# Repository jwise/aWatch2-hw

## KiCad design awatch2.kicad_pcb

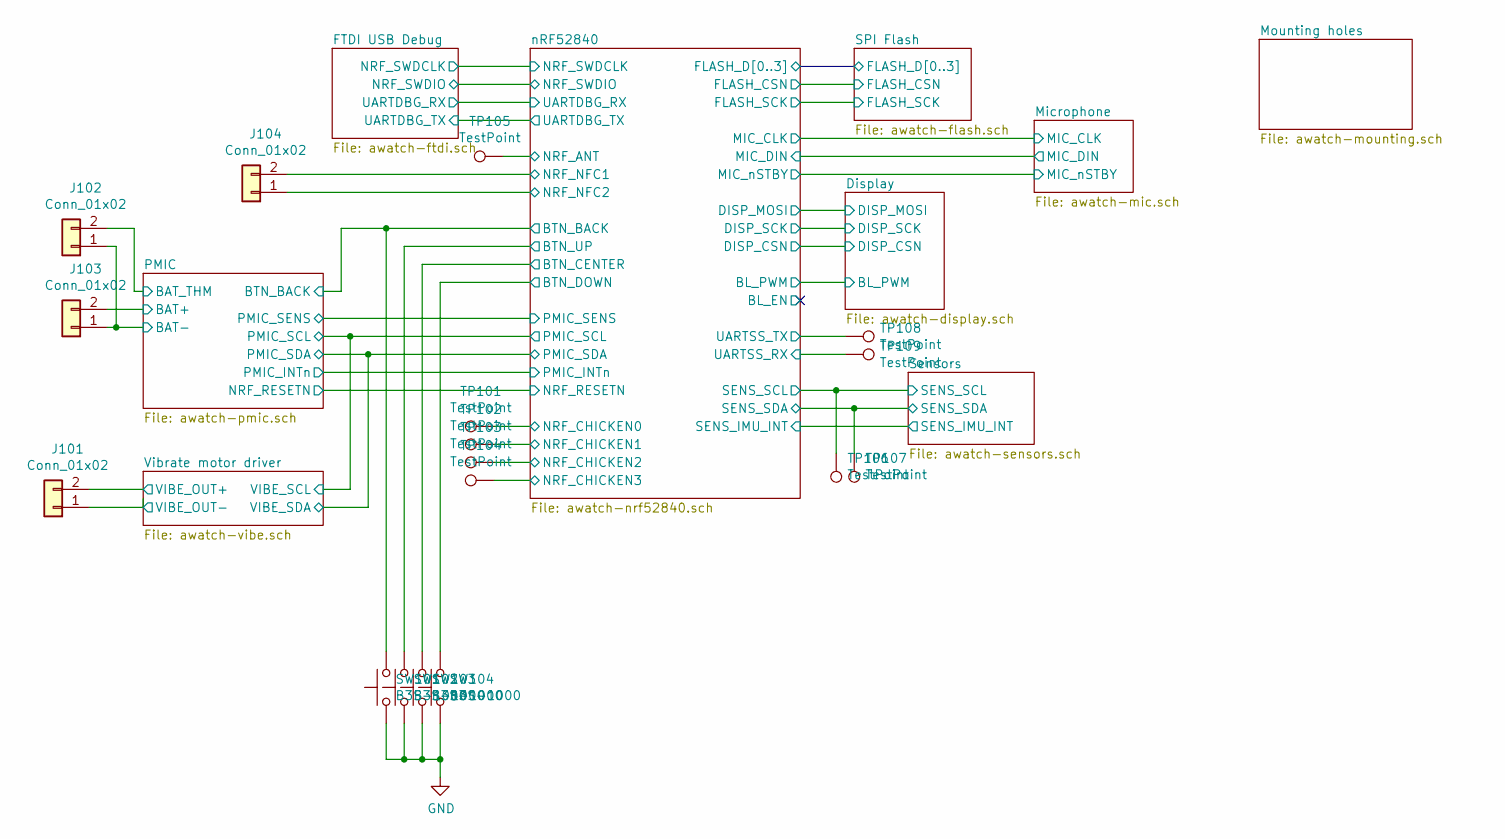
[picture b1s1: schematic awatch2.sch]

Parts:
J101, J102, J103, J104: Conn_01x02; PinHeader_1x02_P2.54mm_Vertical; DigiKey PN S1011EC-02-ND, S9341-ND
SW101, SW102, SW103, SW104: B3S-1000; SW_SPST_B3S-1000; DigiKey PN SW836CT-ND
TP101, TP102, TP103, TP104, TP105, TP106, TP107, TP108, TP109: TestPoint; TestPoint_Pad_D1.5mm

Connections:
/PMIC/BAT+: J103.2; also elsewhere on the board
/PMIC/BAT_THM: J102.2; also elsewhere on the board
/PMIC/BTN_BACK: SW101.2; also elsewhere on the board
/Sensors/SENS_SCL: TP106.1; also elsewhere on the board
/Sensors/SENS_SDA: TP107.1; also elsewhere on the board
/Vibrate motor driver/VIBE_OUT+: J101.2; also elsewhere on the board
/Vibrate motor driver/VIBE_OUT-: J101.1; also elsewhere on the board
/nRF52840/BTN_CENTER: SW103.2; also elsewhere on the board
/nRF52840/BTN_DOWN: SW104.2; also elsewhere on the board
/nRF52840/BTN_UP: SW102.2; also elsewhere on the board
/nRF52840/NRF_ANT: TP105.1; also elsewhere on the board
/nRF52840/NRF_CHICKEN0: TP101.1; also elsewhere on the board
/nRF52840/NRF_CHICKEN1: TP102.1; also elsewhere on the board
/nRF52840/NRF_CHICKEN2: TP103.1; also elsewhere on the board
/nRF52840/NRF_CHICKEN3: TP104.1; also elsewhere on the board
/nRF52840/NRF_NFC1: J104.2; also elsewhere on the board
/nRF52840/NRF_NFC2: J104.1; also elsewhere on the board
/nRF52840/UARTSS_RX: TP109.1; also elsewhere on the board
/nRF52840/UARTSS_TX: TP108.1; also elsewhere on the board
GND: J102.1, J103.1, SW101.1, SW102.1, SW103.1, SW104.1; also elsewhere on the board

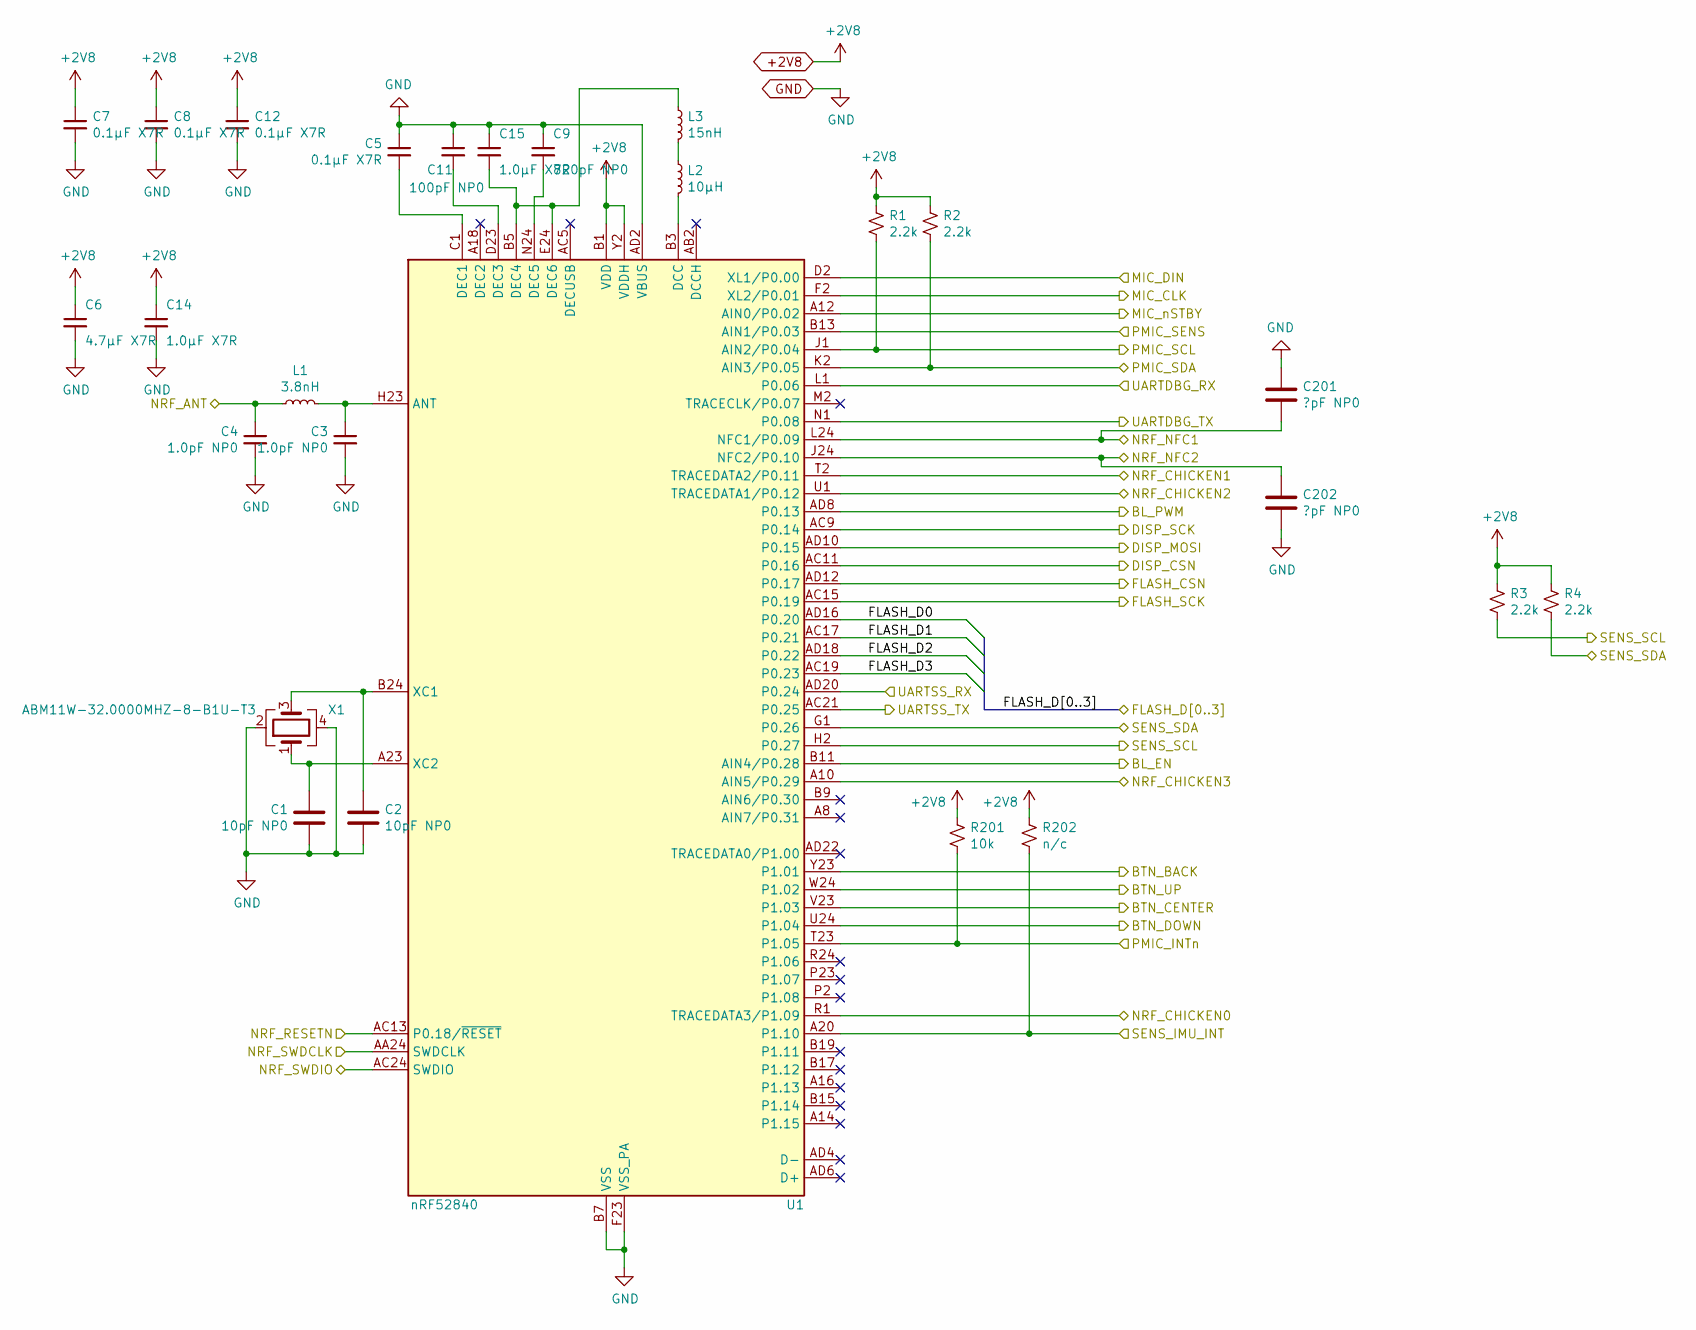
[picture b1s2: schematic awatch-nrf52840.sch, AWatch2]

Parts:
C1, C2: 10pF NP0; C_0603_1608Metric; DigiKey PN 311-3869-1-ND
C3, C4: 1.0pF NP0; C_0603_1608Metric; DigiKey PN 1276-1293-1-ND
C5, C7, C8, C12: 0.1µF X7R; C_0603_1608Metric; DigiKey PN 1276-1061-1-ND
C6: 4.7µF X7R; C_0603_1608Metric; DigiKey PN 1276-2087-1-ND
C9: 820pF NP0; C_0603_1608Metric; DigiKey PN 311-3959-1-ND
C11: 100pF NP0; C_0603_1608Metric; DigiKey PN 311-1069-1-ND
C14, C15: 1.0µF X7R; C_0603_1608Metric; DigiKey PN 1276-1946-1-ND
C201, C202: ?pF NP0; C_0603_1608Metric
L1: 3.8nH; L_0603_1608Metric; DigiKey PN 712-1429-1-ND
L2: 10µH; L_0603_1608Metric; DigiKey PN 445-6755-1-ND
L3: 15nH; L_0603_1608Metric; DigiKey PN CI160808-15NJCT-ND
R1, R2, R3, R4: 2.2k; R_0603_1608Metric; DigiKey PN MCT0603-2.20K-CFCT-ND
R201: 10k; R_0603_1608Metric; DigiKey PN MCT0603-10.0K-CFCT-ND
R202: n/c; R_0603_1608Metric
U1: nRF52840; Nordic_AQFN-73-1EP_7x7mm_P0.5mm; DigiKey PN 1490-1071-1-ND
X1: ABM11W-32.0000MHZ-8-B1U-T3; Crystal_SMD_2016-4Pin_2.0x1.6mm; DigiKey PN 535-13899-1-ND

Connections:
+2V8: C6.1, C7.1, C8.1, C12.1, C14.1, R1.1, R2.1, R3.1, R4.1, R201.1, R202.1, U1.A22 (VDD), U1.AD14 (VDD), U1.AD23 (VDD), U1.B1 (VDD), U1.W1 (VDD), U1.Y2 (VDDH); also elsewhere on the board
/Display/BL_PWM: U1.AD8 (P0.13); also elsewhere on the board
/Display/DISP_CSN: U1.AC11 (P0.16); also elsewhere on the board
/Display/DISP_MOSI: U1.AD10 (P0.15); also elsewhere on the board
/Display/DISP_SCK: U1.AC9 (P0.14); also elsewhere on the board
/FTDI USB Debug/NRF_SWDCLK: U1.AA24 (SWDCLK); also elsewhere on the board
/FTDI USB Debug/NRF_SWDIO: U1.AC24 (SWDIO); also elsewhere on the board
/FTDI USB Debug/UARTDBG_RX: U1.L1 (P0.06); also elsewhere on the board
/FTDI USB Debug/UARTDBG_TX: U1.N1 (P0.08); also elsewhere on the board
/Microphone/MIC_CLK: U1.F2 (XL2/P0.01); also elsewhere on the board
/Microphone/MIC_DIN: U1.D2 (XL1/P0.00); also elsewhere on the board
/Microphone/MIC_nSTBY: U1.A12 (AIN0/P0.02); also elsewhere on the board
/PMIC/BTN_BACK: U1.Y23 (P1.01); also elsewhere on the board
/PMIC/NRF_RESETN: U1.AC13 (P0.18/~RESET); also elsewhere on the board
/PMIC/PMIC_INTn: R201.2, U1.T23 (P1.05); also elsewhere on the board
/PMIC/PMIC_SCL: R1.2, U1.J1 (AIN2/P0.04); also elsewhere on the board
/PMIC/PMIC_SDA: R2.2, U1.K2 (AIN3/P0.05); also elsewhere on the board
/PMIC/PMIC_SENS: U1.B13 (AIN1/P0.03); also elsewhere on the board
/SPI Flash/FLASH_CSN: U1.AD12 (P0.17); also elsewhere on the board
/SPI Flash/FLASH_D0: U1.AD16 (P0.20); also elsewhere on the board
/SPI Flash/FLASH_D1: U1.AC17 (P0.21); also elsewhere on the board
/SPI Flash/FLASH_D2: U1.AD18 (P0.22); also elsewhere on the board
/SPI Flash/FLASH_D3: U1.AC19 (P0.23); also elsewhere on the board
/SPI Flash/FLASH_SCK: U1.AC15 (P0.19); also elsewhere on the board
/Sensors/SENS_IMU_INT: R202.2, U1.A20 (P1.10); also elsewhere on the board
/Sensors/SENS_SCL: R3.2, U1.H2 (P0.27); also elsewhere on the board
/Sensors/SENS_SDA: R4.2, U1.G1 (P0.26); also elsewhere on the board
/nRF52840/BL_EN: U1.B11 (AIN4/P0.28)
/nRF52840/BTN_CENTER: U1.V23 (P1.03); also elsewhere on the board
/nRF52840/BTN_DOWN: U1.U24 (P1.04); also elsewhere on the board
/nRF52840/BTN_UP: U1.W24 (P1.02); also elsewhere on the board
/nRF52840/NRF_ANT: C4.1, L1.1; also elsewhere on the board
/nRF52840/NRF_CHICKEN0: U1.R1 (TRACEDATA3/P1.09); also elsewhere on the board
/nRF52840/NRF_CHICKEN1: U1.T2 (TRACEDATA2/P0.11); also elsewhere on the board
/nRF52840/NRF_CHICKEN2: U1.U1 (TRACEDATA1/P0.12); also elsewhere on the board
/nRF52840/NRF_CHICKEN3: U1.A10 (AIN5/P0.29); also elsewhere on the board
/nRF52840/NRF_NFC1: C201.2, U1.L24 (NFC1/P0.09); also elsewhere on the board
/nRF52840/NRF_NFC2: C202.1, U1.J24 (NFC2/P0.10); also elsewhere on the board
/nRF52840/UARTSS_RX: U1.AD20 (P0.24); also elsewhere on the board
/nRF52840/UARTSS_TX: U1.AC21 (P0.25); also elsewhere on the board
GND: C1.2, C2.2, C3.2, C4.2, C5.1, C6.2, C7.2, C8.2, C9.1, C11.1, C12.2, C14.2, C15.1, C201.1, C202.2, U1.AD2 (VBUS), U1.B7 (VSS), U1.EP (VSS), U1.F23 (VSS_PA), X1.2, X1.4; also elsewhere on the board
unnamed: C1.1, U1.A23 (XC2), X1.1
unnamed: C2.1, U1.B24 (XC1), X1.3
unnamed: C3.1, L1.2, U1.H23 (ANT)
unnamed: C5.2, U1.C1 (DEC1)
unnamed: C9.2, U1.N24 (DEC5)
unnamed: C11.2, U1.D23 (DEC3)
unnamed: C15.2, L3.1, U1.B5 (DEC4), U1.E24 (DEC6)
unnamed: L2.1, L3.2
unnamed: L2.2, U1.B3 (DCC)

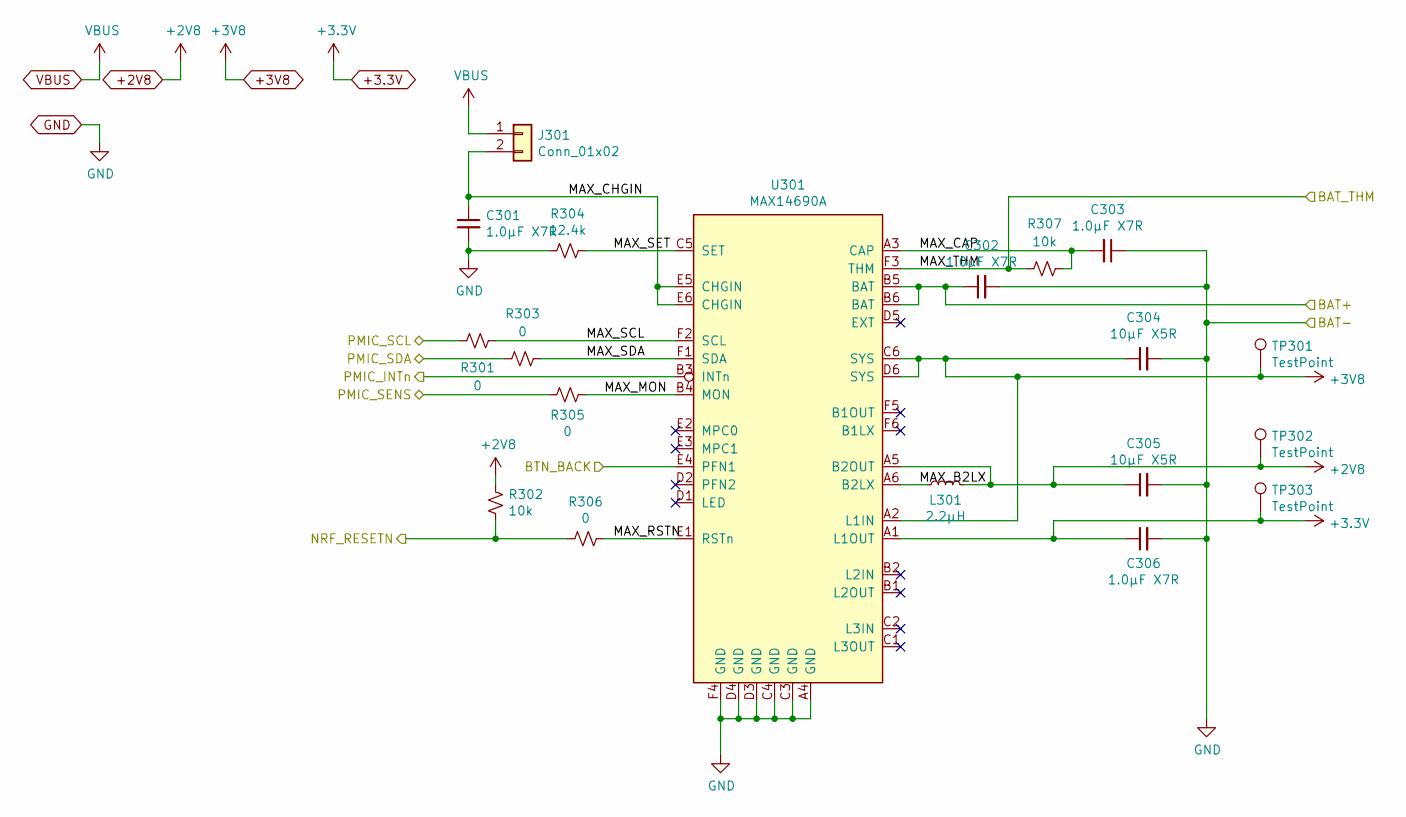
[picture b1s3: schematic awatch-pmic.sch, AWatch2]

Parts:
C301, C302, C303, C306: 1.0µF X7R; C_0603_1608Metric; DigiKey PN 1276-1946-1-ND
C304, C305: 10µF X5R; C_0603_1608Metric; DigiKey PN 490-12538-1-ND
J301: Conn_01x02; PinHeader_1x02_P2.54mm_Vertical; DigiKey PN S1011EC-02-ND, S9341-ND
L301: 2.2µH; L_0603_1608Metric; DigiKey PN 445-6385-1-ND
R301, R303, R305, R306: 0; R_0603_1608Metric; DigiKey PN MCT0603-0.0-ZZCT-ND
R302, R307: 10k; R_0603_1608Metric; DigiKey PN MCT0603-10.0K-CFCT-ND
R304: 12.4k; R_0603_1608Metric; DigiKey PN RNCP0603FTD12K4CT-ND
TP301, TP302, TP303: TestPoint; TestPoint_Pad_D1.5mm
U301: MAX14690A; WLP-36_2.69x2.44mm_Layout6x6_P0.4mm_Ball0.22mm_Pad0.2mm_NSMD; DigiKey PN MOUSER: 700-MAX14690AEWX+

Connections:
+2V8: C305.1, L301.2, R302.2, TP302.1, U301.A5 (B2OUT); also elsewhere on the board
+3.3V: C306.1, TP303.1, U301.A1 (L1OUT); also elsewhere on the board
+3V8: C304.1, TP301.1, U301.A2 (L1IN), U301.C6 (SYS), U301.D6 (SYS); also elsewhere on the board
/PMIC/BAT+: C302.1, U301.B5 (BAT), U301.B6 (BAT); also elsewhere on the board
/PMIC/BAT_THM: R307.2, U301.F3 (THM); also elsewhere on the board
/PMIC/BTN_BACK: U301.E4 (PFN1); also elsewhere on the board
/PMIC/MAX_B2LX: L301.1, U301.A6 (B2LX)
/PMIC/MAX_CAP: C303.2, R307.1, U301.A3 (CAP)
/PMIC/MAX_CHGIN: C301.1, J301.2, U301.E5 (CHGIN), U301.E6 (CHGIN)
/PMIC/MAX_MON: R305.1, U301.B4 (MON)
/PMIC/MAX_RSTN: R306.1, U301.E1 (RSTn)
/PMIC/MAX_SCL: R301.1, U301.F2 (SCL)
/PMIC/MAX_SDA: R303.1, U301.F1 (SDA)
/PMIC/MAX_SET: R304.1, U301.C5 (SET)
/PMIC/NRF_RESETN: R302.1, R306.2; also elsewhere on the board
/PMIC/PMIC_INTn: U301.B3 (INTn); also elsewhere on the board
/PMIC/PMIC_SCL: R301.2; also elsewhere on the board
/PMIC/PMIC_SDA: R303.2; also elsewhere on the board
/PMIC/PMIC_SENS: R305.2; also elsewhere on the board
GND: C301.2, C302.2, C303.1, C304.2, C305.2, C306.2, R304.2, U301.A4 (GND), U301.C3 (GND), U301.C4 (GND), U301.D3 (GND), U301.D4 (GND), U301.F4 (GND); also elsewhere on the board
VBUS: J301.1; also elsewhere on the board

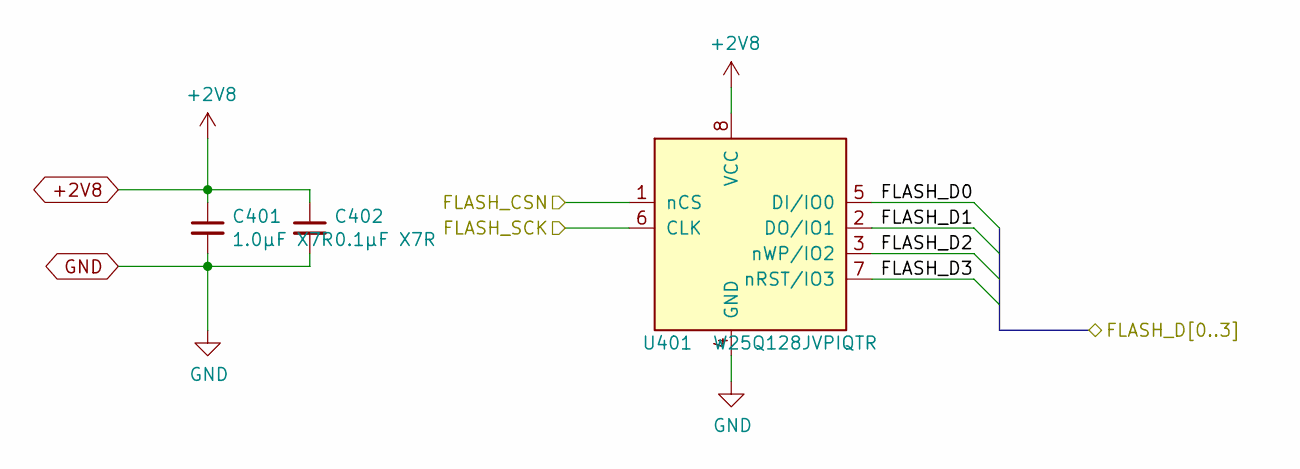
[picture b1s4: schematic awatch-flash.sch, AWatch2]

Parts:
C401: 1.0µF X7R; C_0603_1608Metric; DigiKey PN 1276-1946-1-ND
C402: 0.1µF X7R; C_0603_1608Metric; DigiKey PN 1276-1061-1-ND
U401: W25Q128JVPIQTR; WSON-8-1EP_6x5mm_P1.27mm_EP3.4x4mm; DigiKey PN W25Q128JVPIQCT-ND

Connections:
+2V8: C401.1, C402.1, U401.8 (VCC); also elsewhere on the board
/SPI Flash/FLASH_CSN: U401.1 (nCS); also elsewhere on the board
/SPI Flash/FLASH_D0: U401.5 (DI/IO0); also elsewhere on the board
/SPI Flash/FLASH_D1: U401.2 (DO/IO1); also elsewhere on the board
/SPI Flash/FLASH_D2: U401.3 (nWP/IO2); also elsewhere on the board
/SPI Flash/FLASH_D3: U401.7 (nRST/IO3); also elsewhere on the board
/SPI Flash/FLASH_SCK: U401.6 (CLK); also elsewhere on the board
GND: C401.2, C402.2, U401.4 (GND); also elsewhere on the board

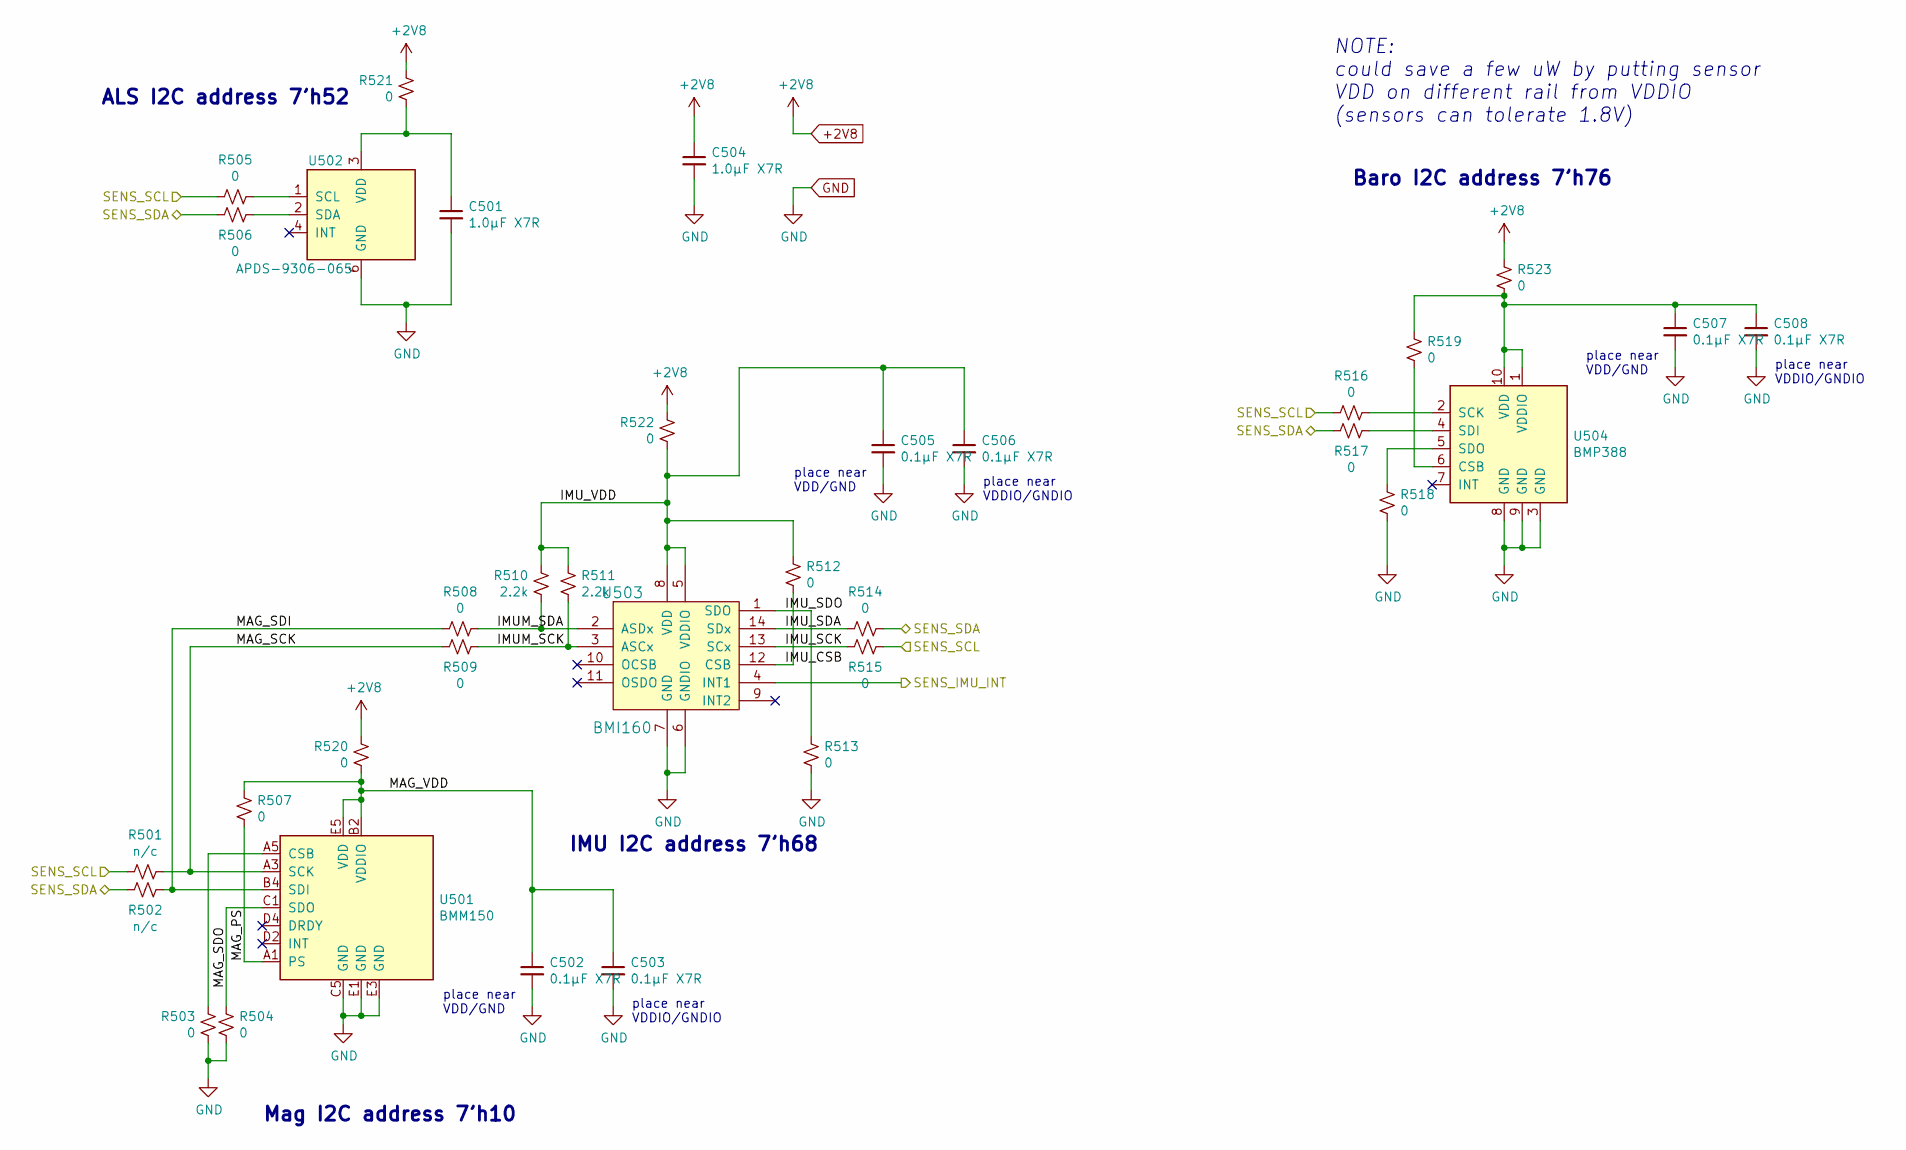
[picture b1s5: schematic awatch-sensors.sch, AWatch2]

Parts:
C501, C504: 1.0µF X7R; C_0603_1608Metric; DigiKey PN 1276-1946-1-ND
C502, C503, C505, C506, C507, C508: 0.1µF X7R; C_0603_1608Metric; DigiKey PN 1276-1061-1-ND
R501, R502: n/c; R_0603_1608Metric
R503, R504, R505, R506, R507, R508, R509, R512, R513, R514, R515, R516, R517, R518, R519, R520, R521, R522, R523: 0; R_0603_1608Metric; DigiKey PN MCT0603-0.0-ZZCT-ND
R510, R511: 2.2k; R_0603_1608Metric; DigiKey PN MCT0603-2.20K-CFCT-ND
U501: BMM150; WLCSP-12_1.56x1.56mm_Layout5x5_P0.283mm_Ball0.25mm_Pad0.2mm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; DigiKey PN 828-1044-1-ND
U502: APDS-9306-065; DFN-6_2x2mm_P0.53mm; DigiKey PN 516-3578-1-ND
U503: BMI160; DigiKey PN 828-1057-1-ND
U504: BMP388; DigiKey PN 828-1079-1-ND

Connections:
+2V8: C504.1, R520.2, R521.2, R522.2, R523.2; also elsewhere on the board
/Sensors/IMUM_SCK: R509.1, R511.2, U503.3 (ASCx)
/Sensors/IMUM_SDA: R508.1, R510.2, U503.2 (ASDx)
/Sensors/IMU_CSB: R512.1, U503.12 (CSB)
/Sensors/IMU_SCK: R515.2, U503.13 (SCx)
/Sensors/IMU_SDA: R514.2, U503.14 (SDx)
/Sensors/IMU_SDO: R513.2, U503.1 (SDO)
/Sensors/IMU_VDD: C505.1, C506.1, R510.1, R511.1, R512.2, R522.1, U503.5 (VDDIO), U503.8 (VDD)
/Sensors/MAG_PS: R507.1, U501.A1 (PS)
/Sensors/MAG_SCK: R501.1, R509.2, U501.A3 (SCK)
/Sensors/MAG_SDI: R502.1, R508.2, U501.B4 (SDI)
/Sensors/MAG_SDO: R504.2, U501.C1 (SDO)
/Sensors/MAG_VDD: C502.1, C503.1, R507.2, R520.1, U501.B2 (VDDIO), U501.E5 (VDD)
/Sensors/SENS_IMU_INT: U503.4 (INT1); also elsewhere on the board
/Sensors/SENS_SCL: R501.2, R505.2, R515.1, R516.2; also elsewhere on the board
/Sensors/SENS_SDA: R502.2, R506.2, R514.1, R517.2; also elsewhere on the board
GND: C501.2, C502.2, C503.2, C504.2, C505.2, C506.2, C507.2, C508.2, R503.1, R504.1, R513.1, R518.1, U501.C5 (GND), U501.E1 (GND), U501.E3 (GND), U502.6 (GND), U503.6 (GNDIO), U503.7 (GND), U504.3 (GND), U504.8 (GND), U504.9 (GND); also elsewhere on the board
unnamed: C501.1, R521.1, U502.3 (VDD)
unnamed: C507.1, C508.1, R519.2, R523.1, U504.1 (VDDIO), U504.10 (VDD)
unnamed: R503.2, U501.A5 (CSB)
unnamed: R505.1, U502.1 (SCL)
unnamed: R506.1, U502.2 (SDA)
unnamed: R516.1, U504.2 (SCK)
unnamed: R517.1, U504.4 (SDI)
unnamed: R518.2, U504.5 (SDO)
unnamed: R519.1, U504.6 (CSB)

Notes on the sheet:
ALS I2C address 7’h52
place near VDDIO/GNDIO
place near VDD/GND
Mag I2C address 7’h10
IMU I2C address 7’h68
Baro I2C address 7’h76
NOTE: could save a few uW by putting sensor VDD on different rail from VDDIO (sensors can tolerate 1.8V)

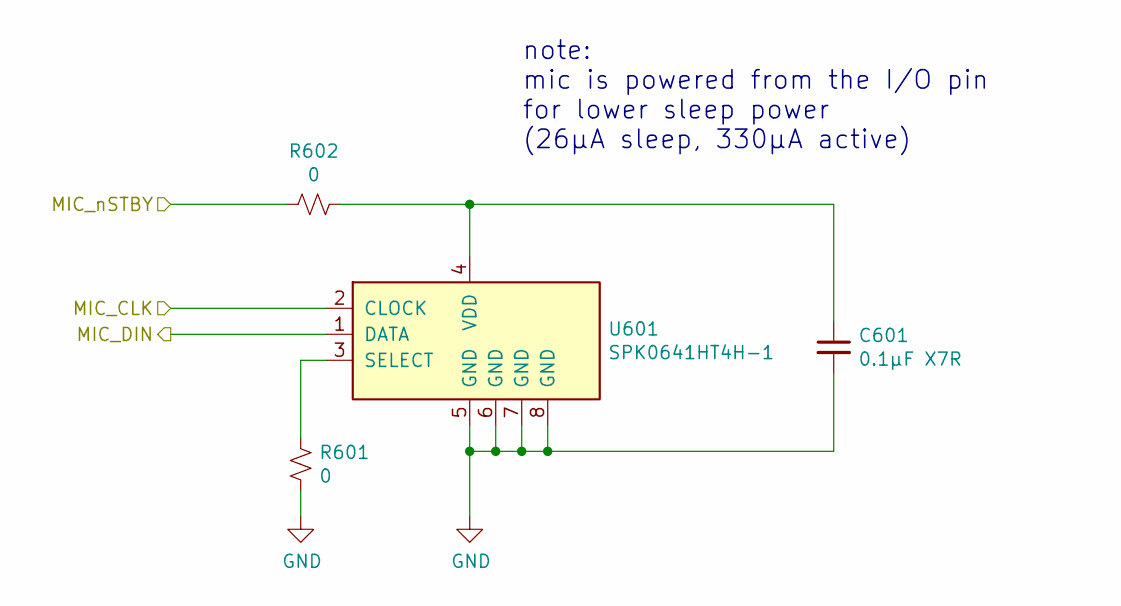
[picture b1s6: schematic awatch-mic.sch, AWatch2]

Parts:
C601: 0.1µF X7R; C_0603_1608Metric; DigiKey PN 1276-1061-1-ND
R601, R602: 0; R_0603_1608Metric; DigiKey PN MCT0603-0.0-ZZCT-ND
U601: SPK0641HT4H-1; SPK0641HT4H; DigiKey PN 423-1425-1-ND

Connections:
/Microphone/MIC_CLK: U601.2 (CLOCK); also elsewhere on the board
/Microphone/MIC_DIN: U601.1 (DATA); also elsewhere on the board
/Microphone/MIC_nSTBY: R602.2; also elsewhere on the board
GND: C601.2, R601.1, U601.5 (GND), U601.6 (GND), U601.7 (GND), U601.8 (GND); also elsewhere on the board
unnamed: C601.1, R602.1, U601.4 (VDD)
unnamed: R601.2, U601.3 (SELECT)

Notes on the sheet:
note: mic is powered from the I/O pin for lower sleep power (26µA sleep, 330µA active)

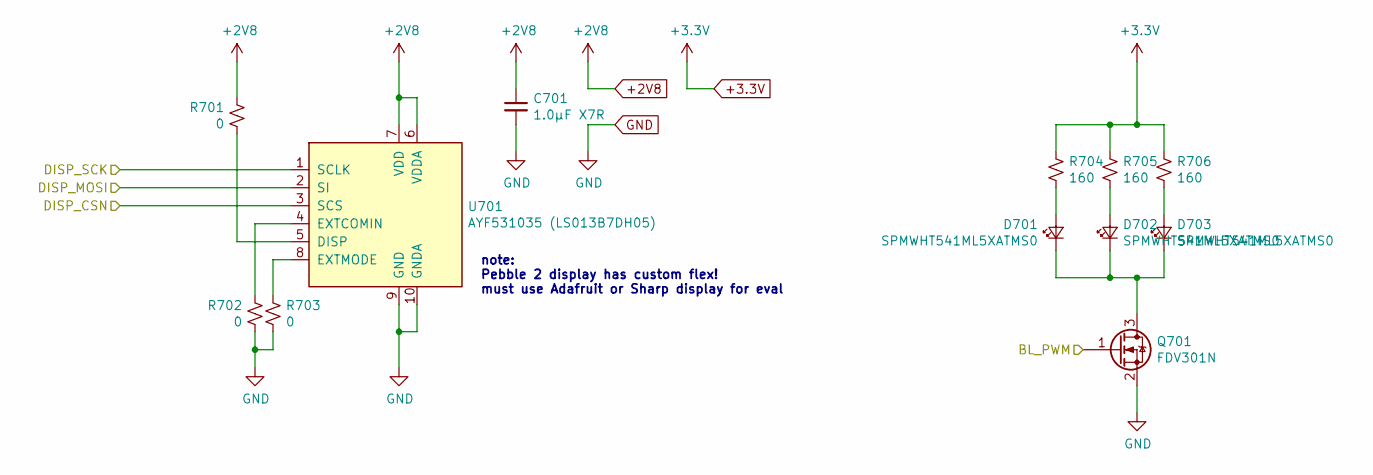
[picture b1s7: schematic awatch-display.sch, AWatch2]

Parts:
C701: 1.0µF X7R; C_0603_1608Metric; DigiKey PN 1276-1946-1-ND
D701, D702, D703: SPMWHT541ML5XATMS0; LED_PLCC_2835_Handsoldering; DigiKey PN 1510-1284-1-ND
Q701: FDV301N; SOT-23; DigiKey PN FDV301NCT-ND
R701, R702, R703: 0; R_0603_1608Metric; DigiKey PN MCT0603-0.0-ZZCT-ND
R704, R705, R706: 160; R_0603_1608Metric; DigiKey PN 749-1765-1-ND
U701: AYF531035 (LS013B7DH05); Panasonic_Y5B_AYF531035_1x10-1MP_P0.50mm_Horizontal; DigiKey PN 255-5667-ND, Adafruit display

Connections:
+2V8: C701.1, R701.1, U701.6 (VDDA), U701.7 (VDD); also elsewhere on the board
+3.3V: R704.1, R705.1, R706.1; also elsewhere on the board
/Display/BL_PWM: Q701.1 (G); also elsewhere on the board
/Display/DISP_CSN: U701.3 (SCS); also elsewhere on the board
/Display/DISP_MOSI: U701.2 (SI); also elsewhere on the board
/Display/DISP_SCK: U701.1 (SCLK); also elsewhere on the board
GND: C701.2, Q701.2 (S), R702.2, R703.2, U701.9 (GND), U701.10 (GNDA); also elsewhere on the board
unnamed: D701.1 (K), D702.1 (K), D703.1 (K), Q701.3 (D)
unnamed: D701.2 (A), R704.2
unnamed: D702.2 (A), R705.2
unnamed: D703.2 (A), R706.2
unnamed: R701.2, U701.5 (DISP)
unnamed: R702.1, U701.4 (EXTCOMIN)
unnamed: R703.1, U701.8 (EXTMODE)

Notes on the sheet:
note: Pebble 2 display has custom flex! must use Adafruit or Sharp display for eval

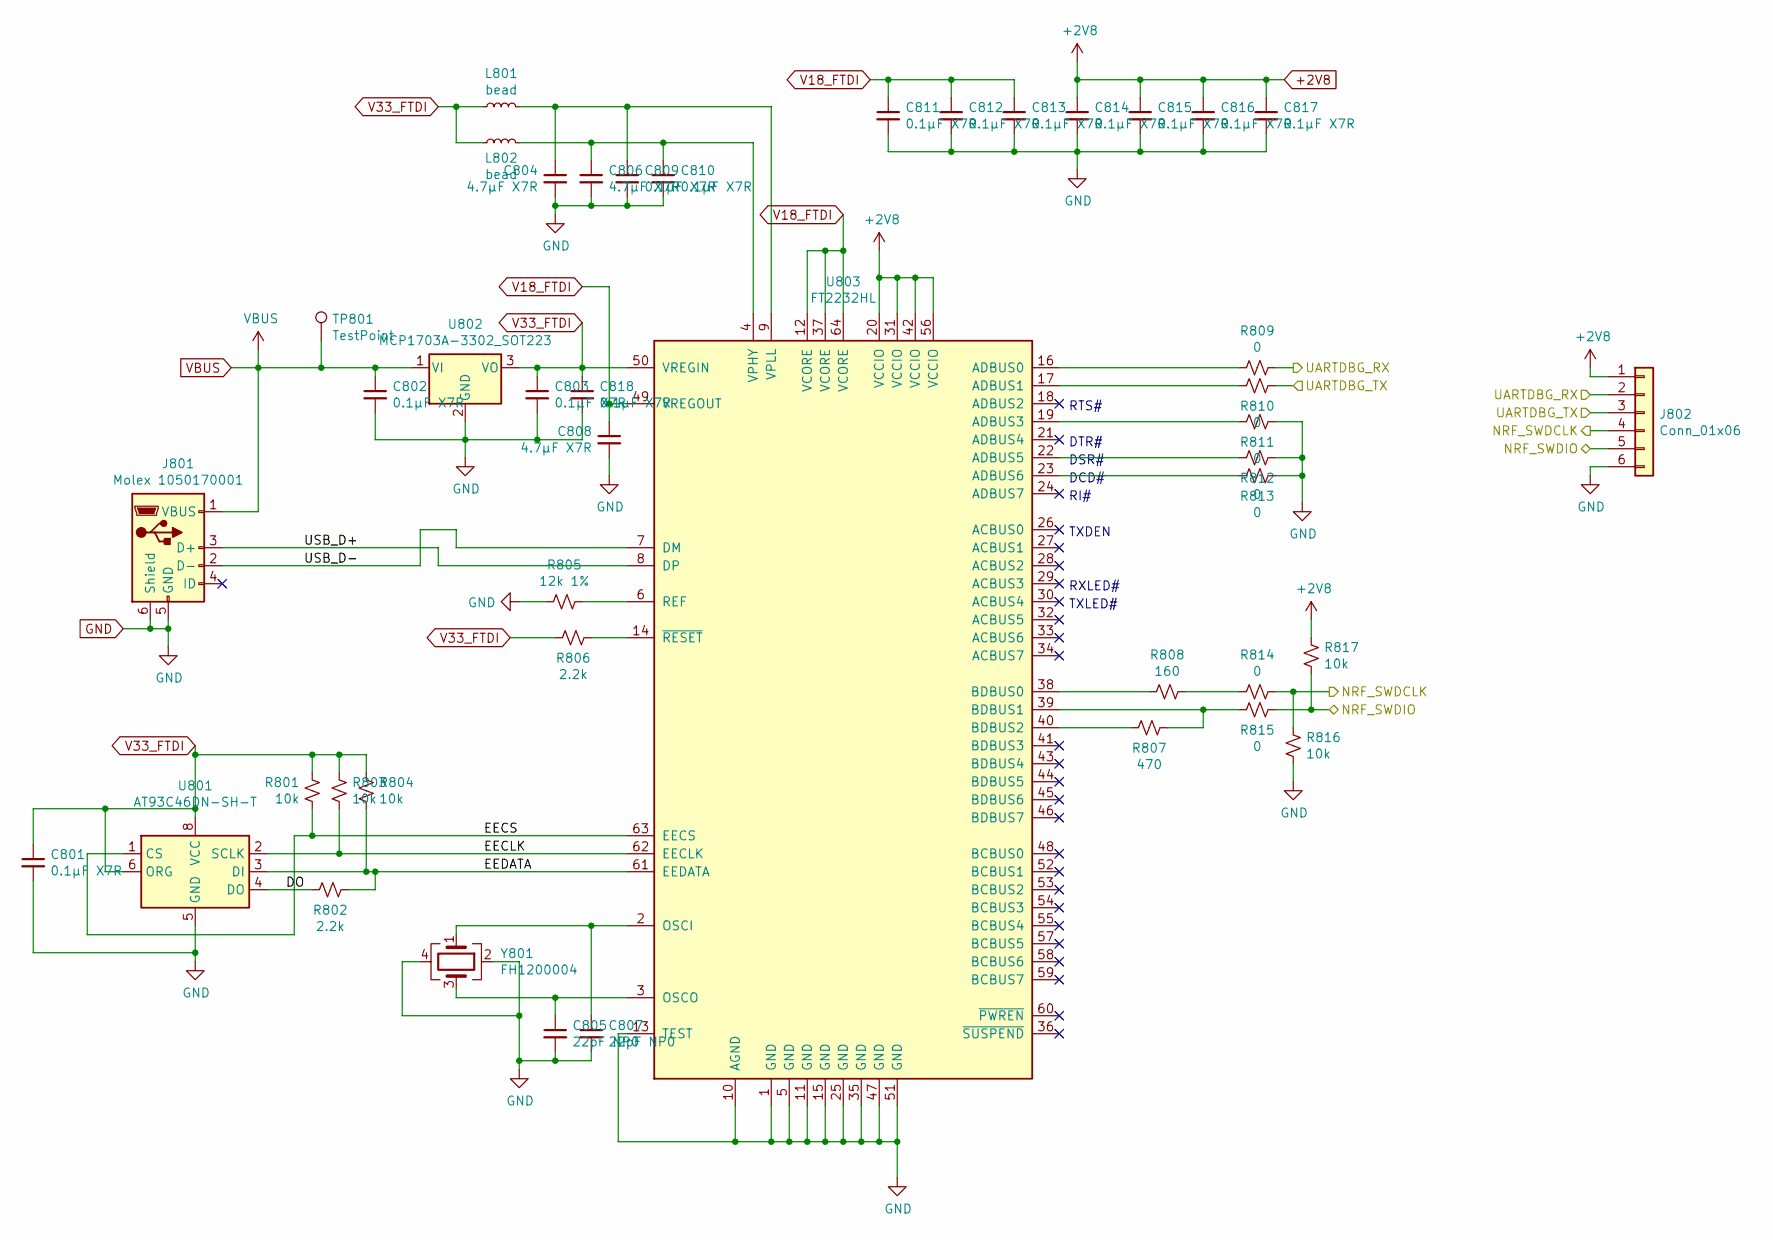
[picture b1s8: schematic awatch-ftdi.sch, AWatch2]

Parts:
C801, C802, C803, C809, C810, C811, C812, C813, C814, C815, C816, C817, C818: 0.1µF X7R; C_0603_1608Metric; DigiKey PN 1276-1061-1-ND
C804, C806, C808: 4.7µF X7R; C_0603_1608Metric; DigiKey PN 1276-2087-1-ND
C805, C807: 22pF NP0; C_0603_1608Metric; DigiKey PN 399-7874-1-ND
J801: Molex 1050170001; USB_Micro-B_Molex-105017-0001; DigiKey PN WM1399CT-ND
J802: Conn_01x06; PinHeader_1x06_P2.54mm_Vertical; DigiKey PN S1011EC-06-ND
L801, L802: bead; L_0603_1608Metric; DigiKey PN 587-1926-1-ND
R801, R803, R804, R816, R817: 10k; R_0603_1608Metric; DigiKey PN MCT0603-10.0K-CFCT-ND
R802, R806: 2.2k; R_0603_1608Metric; DigiKey PN MCT0603-2.20K-CFCT-ND
R805: 12k 1%; R_0603_1608Metric; DigiKey PN MCT0603-12.0K-CFCT-ND
R807: 470; R_0603_1608Metric; DigiKey PN MCT0603-470-CFCT-ND
R808: 160; R_0603_1608Metric; DigiKey PN 749-1765-1-ND
R809, R810, R811, R812, R813, R814, R815: 0; R_0603_1608Metric; DigiKey PN MCT0603-0.0-ZZCT-ND
TP801: TestPoint; TestPoint_Pad_D1.5mm
U801: AT93C46DN-SH-T; SOIC-8_3.9x4.9mm_P1.27mm; DigiKey PN AT93C46DN-SH-TCT-ND AT93C46DN-SH-TCT-ND
U802: MCP1703A-3302_SOT223; SOT-223-3_TabPin2; DigiKey PN MCP1703AT-3302E/DBCT-ND
U803: FT2232HL; LQFP-64_10x10mm_P0.5mm; DigiKey PN 768-1024-1-ND
Y801: FH1200004; Crystal_SMD_2520-4Pin_2.5x2.0mm; DigiKey PN FH1200004CT-ND

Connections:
+2V8: C814.1, C815.1, C816.1, C817.1, J802.1, R817.2, U803.20 (VCCIO), U803.31 (VCCIO), U803.42 (VCCIO), U803.56 (VCCIO); also elsewhere on the board
/FTDI USB Debug/DO: R802.2, U801.4 (DO)
/FTDI USB Debug/EECLK: R803.1, U801.2 (SCLK), U803.62 (EECLK)
/FTDI USB Debug/EECS: R801.1, U801.1 (CS), U803.63 (EECS)
/FTDI USB Debug/EEDATA: R802.1, R804.1, U801.3 (DI), U803.61 (EEDATA)
/FTDI USB Debug/NRF_SWDCLK: J802.4, R814.1, R816.2; also elsewhere on the board
/FTDI USB Debug/NRF_SWDIO: J802.5, R815.1, R817.1; also elsewhere on the board
/FTDI USB Debug/UARTDBG_RX: J802.2, R809.1; also elsewhere on the board
/FTDI USB Debug/UARTDBG_TX: J802.3, R810.1; also elsewhere on the board
/FTDI USB Debug/USB_D+: J801.3 (D+), U803.8 (DP)
/FTDI USB Debug/USB_D-: J801.2 (D-), U803.7 (DM)
GND: C801.2, C802.2, C803.2, C804.2, C805.2, C806.2, C807.2, C808.2, C809.2, C810.2, C811.2, C812.2, C813.2, C814.2, C815.2, C816.2, C817.2, C818.2, J801.5 (GND), J801.6 (Shield), J802.6, R805.1, R811.2, R812.2, R813.2, R816.1, U801.5 (GND), U802.2 (GND), U803.1 (GND), U803.5 (GND), U803.10 (AGND), U803.11 (GND), U803.13 (TEST), U803.15 (GND), U803.25 (GND), U803.35 (GND), U803.47 (GND), U803.51 (GND), Y801.2, Y801.4; also elsewhere on the board
unnamed: C804.1, C809.1, L801.2, U803.9 (VPLL)
unnamed: C805.1, U803.3 (OSCO), Y801.3
unnamed: C806.1, C810.1, L802.2, U803.4 (VPHY)
unnamed: C807.1, U803.2 (OSCI), Y801.1
unnamed: R805.2, U803.6 (REF)
unnamed: R806.2, U803.14 (~RESET)
unnamed: R807.1, R815.2, U803.39 (BDBUS1)
unnamed: R807.2, U803.40 (BDBUS2)
unnamed: R808.1, R814.2
unnamed: R808.2, U803.38 (BDBUS0)
unnamed: R809.2, U803.16 (ADBUS0)
unnamed: R810.2, U803.17 (ADBUS1)
unnamed: R811.1, U803.19 (ADBUS3)
unnamed: R812.1, U803.22 (ADBUS5)
unnamed: R813.1, U803.23 (ADBUS6)
V18_FTDI: C808.1, C811.1, C812.1, C813.1, U803.12 (VCORE), U803.37 (VCORE), U803.49 (VREGOUT), U803.64 (VCORE)
V33_FTDI: C801.1, C803.1, C818.1, L801.1, L802.1, R801.2, R803.2, R804.2, R806.1, U801.6 (ORG), U801.8 (VCC), U802.3 (VO), U803.50 (VREGIN)
VBUS: C802.1, J801.1 (VBUS), TP801.1, U802.1 (VI); also elsewhere on the board

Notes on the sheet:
RTS#
DTR#
DSR#
DCD#
RI#
TXDEN
RXLED#
TXLED#

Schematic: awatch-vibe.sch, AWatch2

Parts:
C901, C903: 1.0µF X7R; C_0603_1608Metric; DigiKey PN 1276-1946-1-ND
C902: 0.1µF X7R; C_0603_1608Metric; DigiKey PN 1276-1061-1-ND
R901, R902, R903, R904, R905: 0; R_0603_1608Metric; DigiKey PN MCT0603-0.0-ZZCT-ND
U901: DRV2604; Texas_DSBGA-9_1.47x1.47mm_Layout3x3_P0.5mm_NSMD; DigiKey PN 296-45407-1-ND

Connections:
+3V8: R905.2; also elsewhere on the board
/PMIC/PMIC_SCL: R901.2; also elsewhere on the board
/PMIC/PMIC_SDA: R902.2; also elsewhere on the board
/Vibrate motor driver/VIBE_EN: R903.2, U901.A1 (EN)
/Vibrate motor driver/VIBE_IN: R904.2, U901.B1 (IN/TRIG)
/Vibrate motor driver/VIBE_OUT+: U901.A3 (OUT+); also elsewhere on the board
/Vibrate motor driver/VIBE_OUT-: U901.C3 (OUT-); also elsewhere on the board
/Vibrate motor driver/VIBE_REG: C903.1, U901.A2 (REG)
/Vibrate motor driver/VIBE_SCL_IN: R901.1, U901.C1 (SCL)
/Vibrate motor driver/VIBE_SDA_IN: R902.1, U901.B2 (SDA)
/Vibrate motor driver/VIBE_VDD: C901.1, C902.1, R905.1, U901.C2 (VDD)
GND: C901.2, C902.2, C903.2, R903.1, R904.1, U901.B3 (GND); also elsewhere on the board

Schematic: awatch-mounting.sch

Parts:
G1: Logo; littlehatguy
H1001, H1002, H1003, H1004: 6-32
H1005, H1006, H1007: Fiducial; Fiducial_0.5mm_Dia_1mm_Outer

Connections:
GND: H1001.1, H1002.1, H1003.1, H1004.1; also elsewhere on the board
